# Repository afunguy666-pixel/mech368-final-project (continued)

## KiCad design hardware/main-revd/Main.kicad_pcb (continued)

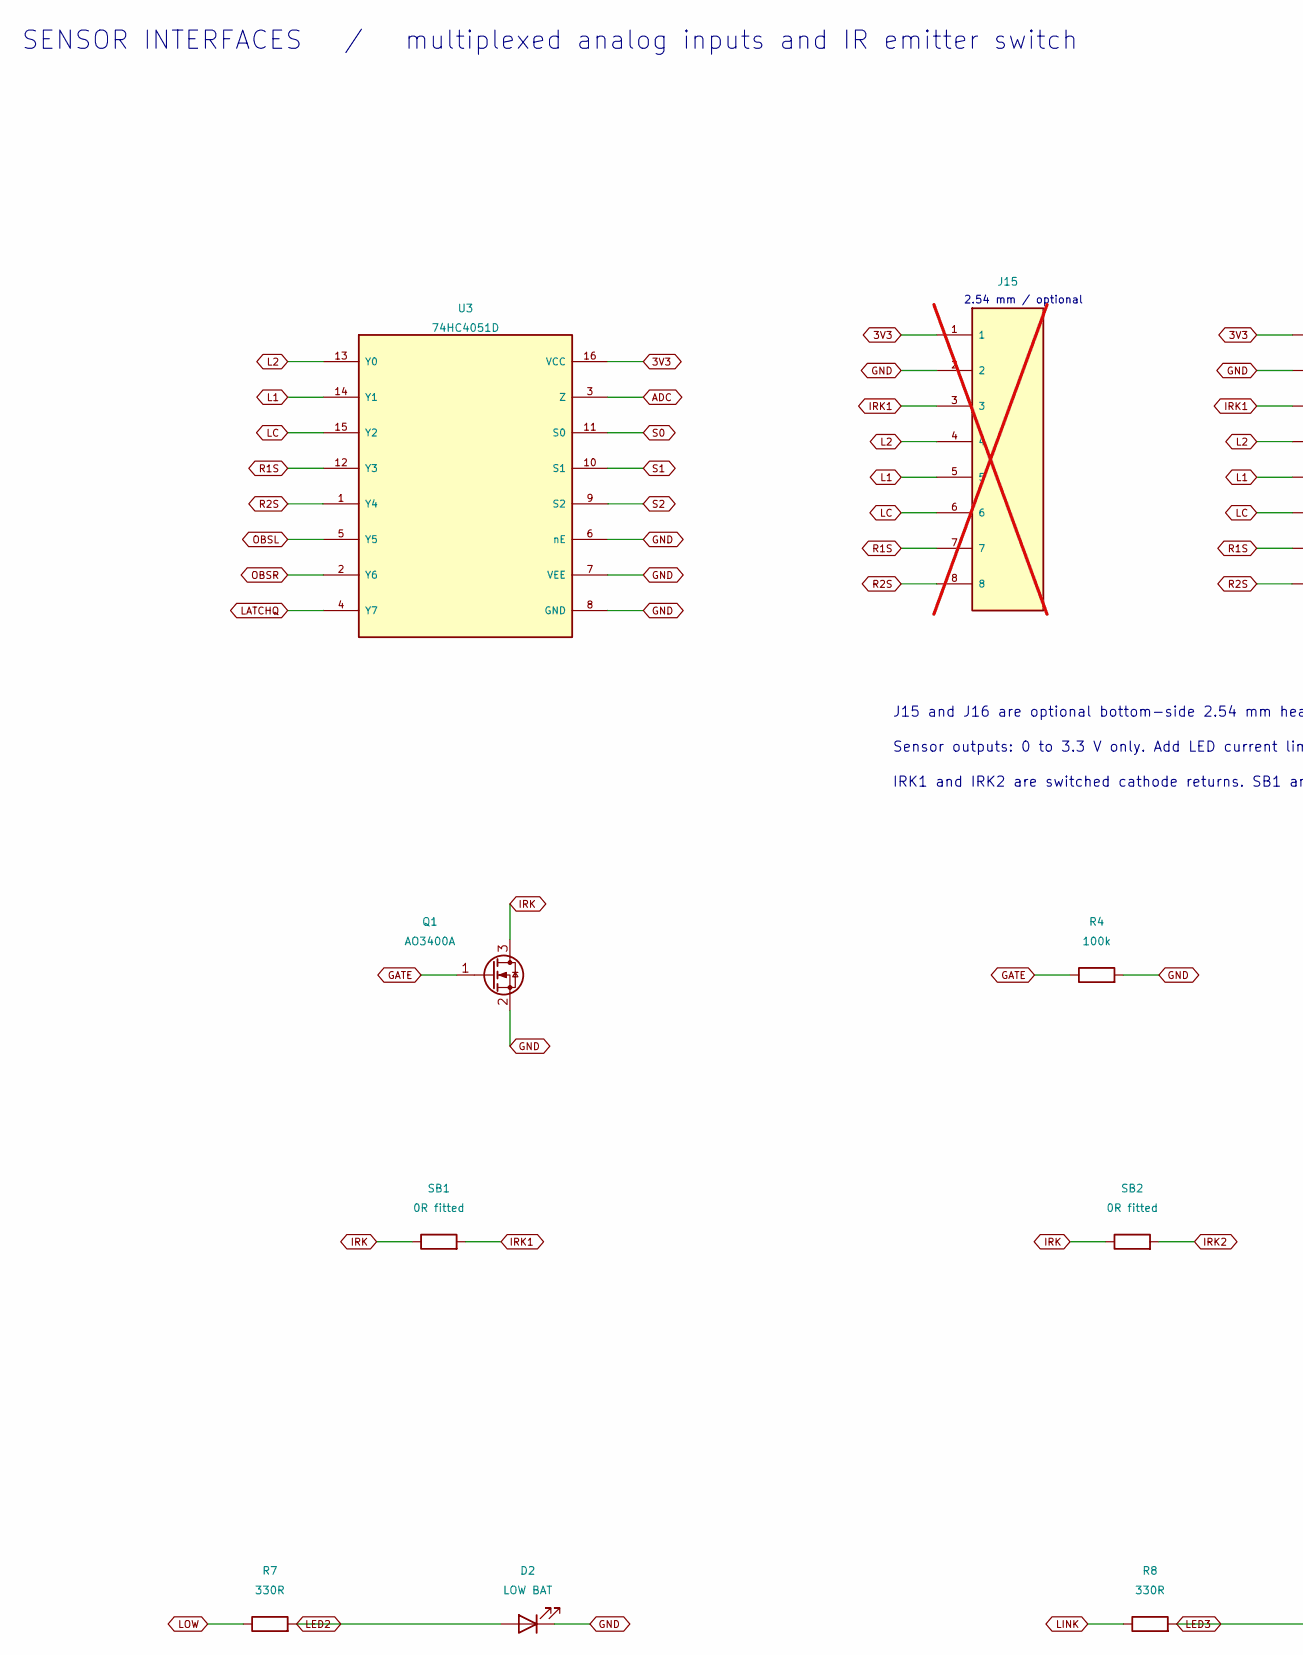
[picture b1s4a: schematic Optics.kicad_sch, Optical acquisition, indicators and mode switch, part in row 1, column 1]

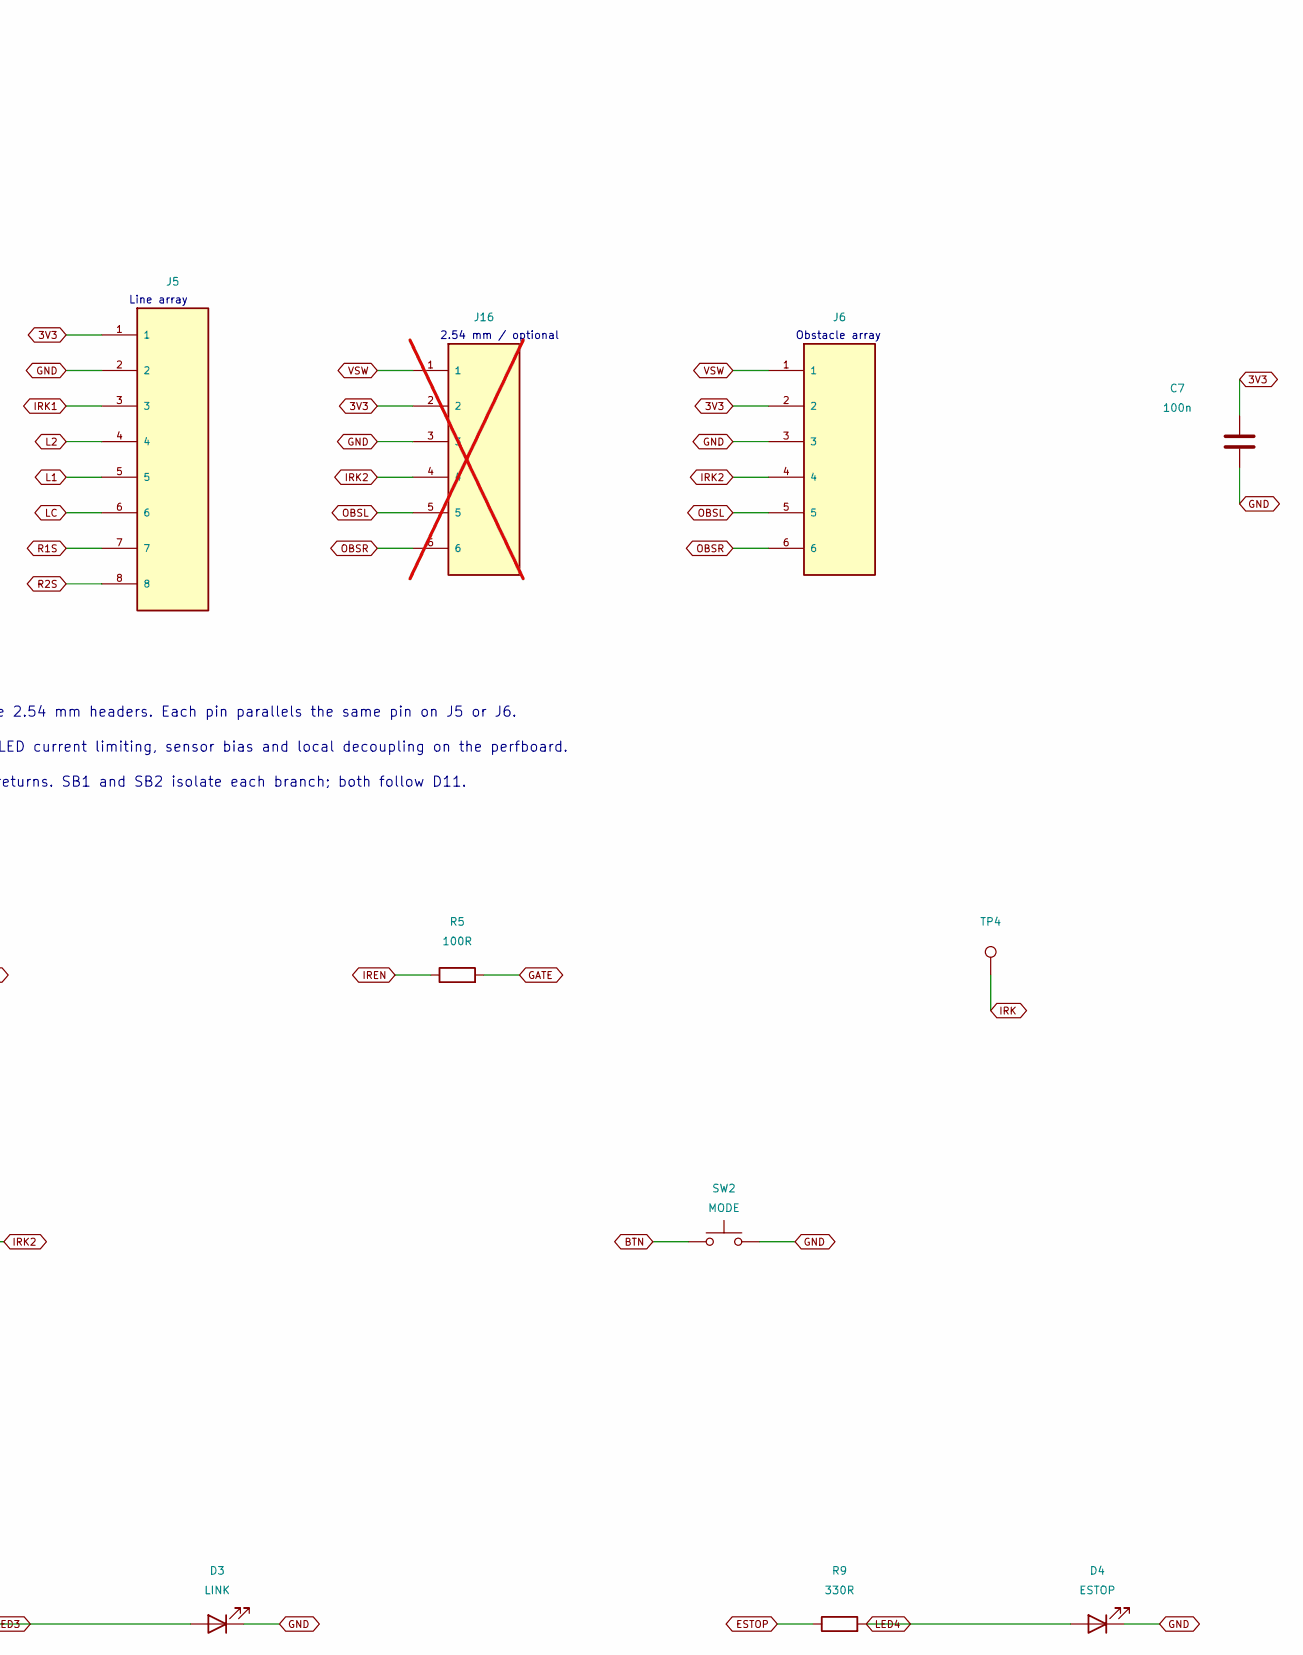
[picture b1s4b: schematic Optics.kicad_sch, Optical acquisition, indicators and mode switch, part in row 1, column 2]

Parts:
C7: 100n; C_0805_2012Metric
D2: LOW BAT; LED_D3.0mm
D3: LINK; LED_D3.0mm
D4: ESTOP; LED_D3.0mm
J5: XH; JST_XH_B8B-XH-A_1x08_P2.50mm_Vertical
J6: XH; JST_XH_B6B-XH-A_1x06_P2.50mm_Vertical
J15: Perfboard 2.54; PinHeader_1x08_P2.54mm_Vertical; not fitted
J16: Perfboard 2.54; PinHeader_1x06_P2.54mm_Vertical; not fitted
Q1: AO3400A; SOT-23
R4: 100k; R_Axial_DIN0207_L6.3mm_D2.5mm_P10.16mm_Horizontal
R5: 100R; R_Axial_DIN0207_L6.3mm_D2.5mm_P10.16mm_Horizontal
R7, R8, R9: 330R; R_Axial_DIN0207_L6.3mm_D2.5mm_P10.16mm_Horizontal
SB1, SB2: 0R fitted; R_Axial_DIN0207_L6.3mm_D2.5mm_P10.16mm_Horizontal
SW2: MODE; SW_PUSH_6mm
TP4: IRK; TestPoint_Pad_D1.5mm
U3: 74HC4051D; SOIC-16_3.9x9.9mm_P1.27mm

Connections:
3V3: C7.1, J5.1, J6.2, J15.1, J16.2, U3.16 (VCC); also elsewhere on the board
ADC: U3.3 (Z); also elsewhere on the board
BTN: SW2.1; also elsewhere on the board
ESTOP: R9.1; also elsewhere on the board
GATE: Q1.1 (G), R4.1, R5.2
GND: C7.2, D2.1 (K), D3.1 (K), D4.1 (K), J5.2, J6.3, J15.2, J16.3, Q1.2 (S), R4.2, SW2.2, U3.6 (nE), U3.7 (VEE), U3.8 (GND); also elsewhere on the board
IREN: R5.1; also elsewhere on the board
IRK: Q1.3 (D), SB1.1, SB2.1, TP4.1
IRK1: J5.3, J15.3, SB1.2
IRK2: J6.4, J16.4, SB2.2
L1: J5.5, J15.5, U3.14 (Y1)
L2: J5.4, J15.4, U3.13 (Y0)
LATCHQ: U3.4 (Y7); also elsewhere on the board
LC: J5.6, J15.6, U3.15 (Y2)
LED2: D2.2 (A), R7.2
LED3: D3.2 (A), R8.2
LED4: D4.2 (A), R9.2
LINK: R8.1; also elsewhere on the board
LOW: R7.1; also elsewhere on the board
OBSL: J6.5, J16.5, U3.5 (Y5)
OBSR: J6.6, J16.6, U3.2 (Y6)
R1S: J5.7, J15.7, U3.12 (Y3)
R2S: J5.8, J15.8, U3.1 (Y4)
S0: U3.11 (S0); also elsewhere on the board
S1: U3.10 (S1); also elsewhere on the board
S2: U3.9 (S2); also elsewhere on the board
VSW: J6.1, J16.1; also elsewhere on the board

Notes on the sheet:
SENSOR INTERFACES / multiplexed analog inputs and IR emitter switch
Line array
Obstacle array
2.54 mm / optional
J15 and J16 are optional bottom-side 2.54 mm headers. Each pin parallels the same pin on J5 or J6.
Sensor outputs: 0 to 3.3 V only. Add LED current limiting, sensor bias and local decoupling on the perfboard.
IRK1 and IRK2 are switched cathode returns. SB1 and SB2 isolate each branch; both follow D11.

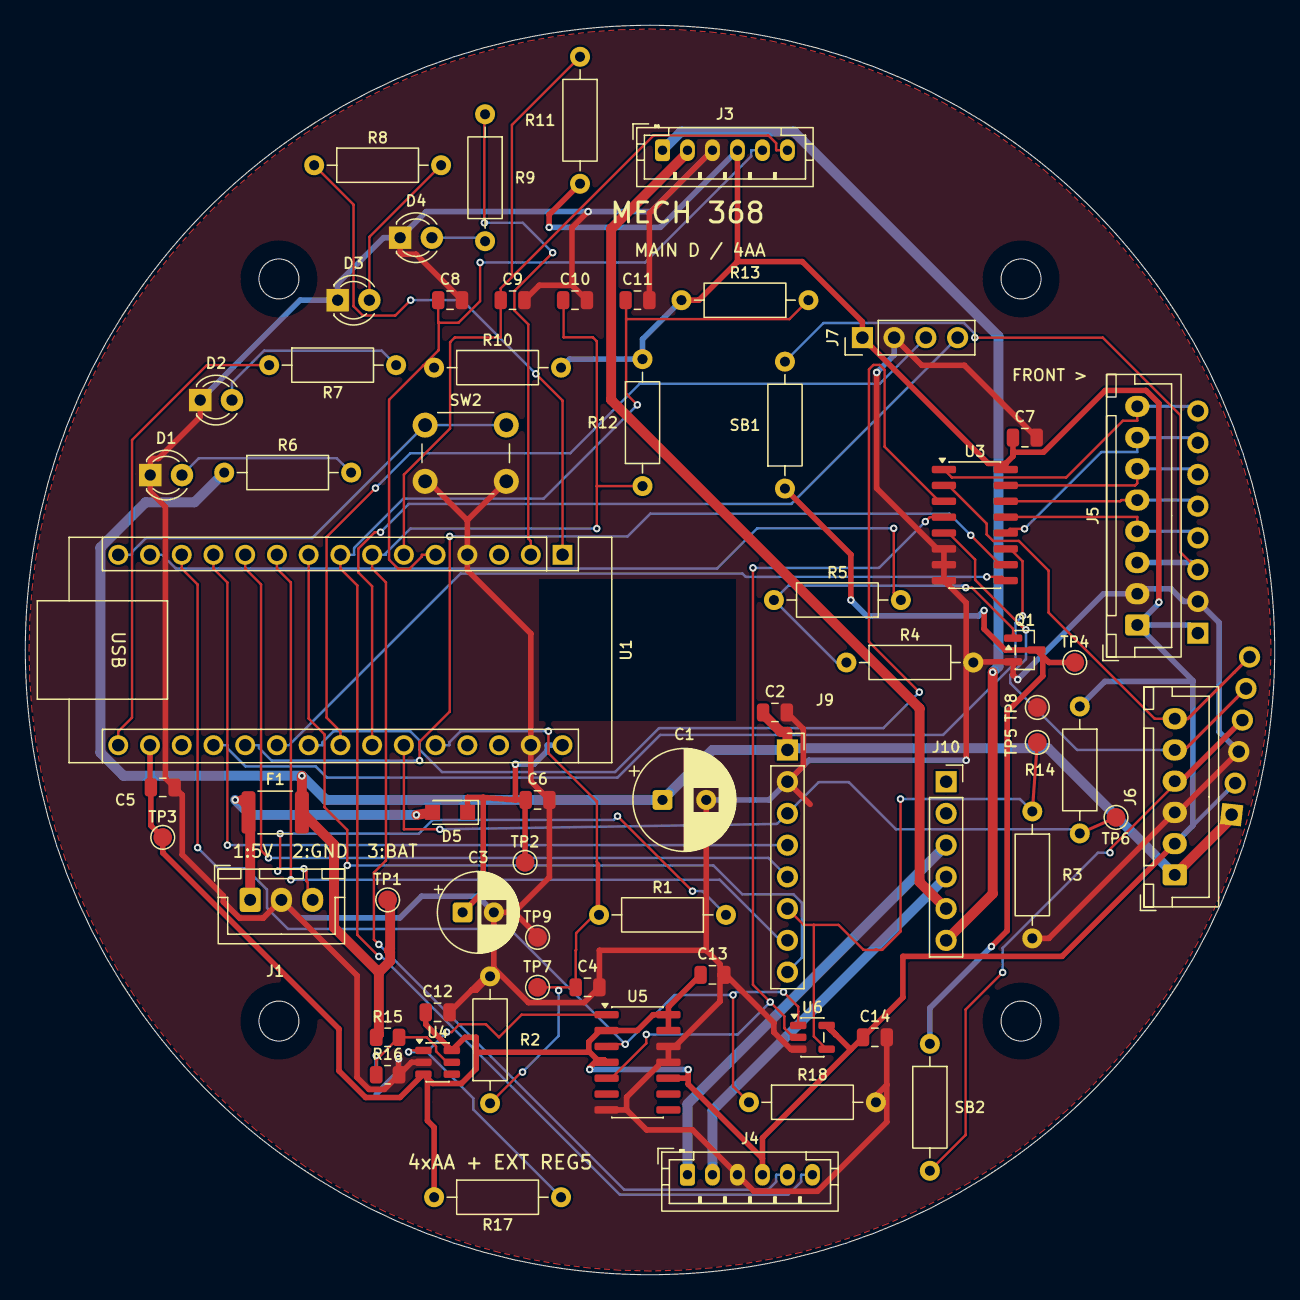
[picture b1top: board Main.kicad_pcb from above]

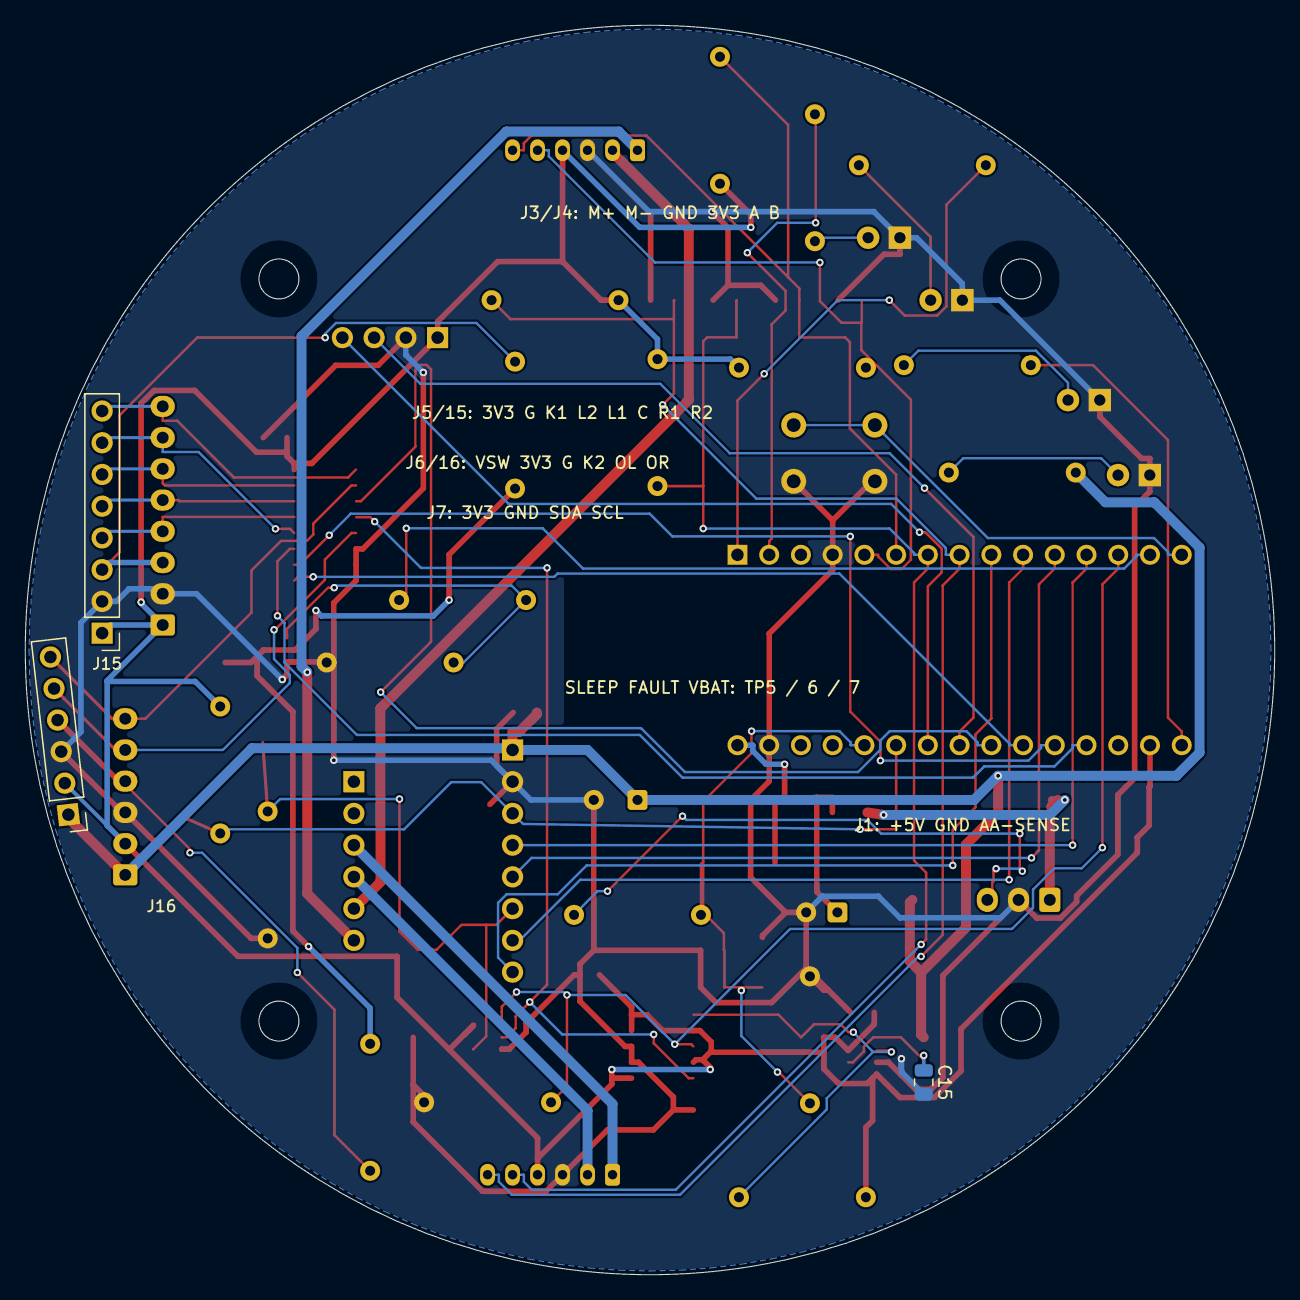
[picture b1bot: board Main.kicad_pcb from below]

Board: 2 copper layers, 100.0 x 100.0 mm, 71 parts (3 on the bottom side), 51 nets.

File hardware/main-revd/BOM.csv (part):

Reference,Value / part,Footprint,Population,Side,Sites,Pad nets,Assembly notes,Default sites for 5 boards,Supply group
C1,470u 16V,Capacitor_THT:CP_Radial_D8.0mm_P3.50mm,FIT,top,1,1=VSW | 2=GND,"Radial 470 uF, >=16 V, diameter <=8 mm, pitch 3.5 mm",5,Procure or existing bench stock
C2,100n,Capacitor_SMD:C_0805_2012Metric,FIT,top,1,1=VSW | 2=GND,,5,Procure or existing bench stock
C3,DNP 220u,Capacitor_THT:CP_Radial_D6.3mm_P2.50mm,DNP,top,1,1=VIN | 2=GND,,0,Optional / DNP
C4,100n,Capacitor_SMD:C_0805_2012Metric,FIT,top,1,1=VBAT_ADC | 2=GND,,5,Procure or existing bench stock
C5,100n,Capacitor_SMD:C_0805_2012Metric,FIT,top,1,1=3V3 | 2=GND,,5,Procure or existing bench stock
C6,10u 25V,Capacitor_SMD:C_0805_2012Metric,FIT,top,1,1=VIN | 2=GND,,5,Procure or existing bench stock
C7,100n,Capacitor_SMD:C_0805_2012Metric,FIT,top,1,1=3V3 | 2=GND,,5,Procure or existing bench stock
C8,DNP 100p,Capacitor_SMD:C_0805_2012Metric,DNP,top,1,1=ELA | 2=GND,,0,Optional / DNP
C9,DNP 100p,Capacitor_SMD:C_0805_2012Metric,DNP,top,1,1=ELB | 2=GND,,0,Optional / DNP
C10,DNP 100p,Capacitor_SMD:C_0805_2012Metric,DNP,top,1,1=ERA | 2=GND,,0,Optional / DNP
C11,DNP 100p,Capacitor_SMD:C_0805_2012Metric,DNP,top,1,1=ERB | 2=GND,,0,Optional / DNP
C12,100n,Capacitor_SMD:C_0805_2012Metric,FIT,top,1,1=3V3 | 2=GND,,5,Procure or existing bench stock
C13,100n,Capacitor_SMD:C_0805_2012Metric,FIT,top,1,1=3V3 | 2=GND,,5,Procure or existing bench stock
C14,100n,Capacitor_SMD:C_0805_2012Metric,FIT,top,1,1=3V3 | 2=GND,,5,Procure or existing bench stock
C15,DNP 10n,Capacitor_SMD:C_0805_2012Metric,DNP,bottom,1,1=UVS | 2=GND,"Optional UVS filter, X7R >=10 V; fit only if motor start/PWM transients falsely clear the latch (tau ~100 us)",0,Optional / DNP
D1,POWER,LED_THT:LED_D3.0mm,FIT,top,1,1=GND | 2=LED1,,5,Procure or existing bench stock
D2,LOW BAT,LED_THT:LED_D3.0mm,FIT,top,1,1=GND | 2=LED2,Visible low-battery indication,5,Procure or existing bench stock
D3,LINK,LED_THT:LED_D3.0mm,FIT,top,1,1=GND | 2=LED3,Visible BLE link / timeout indicator,5,Procure or existing bench stock
D4,ESTOP,LED_THT:LED_D3.0mm,FIT,top,1,1=GND | 2=LED4,Visible emergency stop indicator,5,Procure or existing bench stock
D5,PMEG2010ER K1,Diode_SMD:Nexperia_CFP3_SOD-123W,FIT,top,1,1=VIN | 2=REG5V,Nexperia PMEG2010ER; bar = pad 1 = VIN (east); anode on REG5V ahead of F1,5,Procure or existing bench stock
F1,1812L150/16DR 1.5A,Fuse:Fuse_1812_4532Metric,FIT,top,1,1=REG5V | 2=VSW,Littelfuse 1812L150/16DR; downstream PPTC,5,Procure or existing bench stock
H1,MountingHole_3.2mm_M3,MountingHole:MountingHole_3.2mm_M3,PCB FEATURE,top,1,,,0,PCB feature
H2,MountingHole_3.2mm_M3,MountingHole:MountingHole_3.2mm_M3,PCB FEATURE,top,1,,,0,PCB feature
H3,MountingHole_3.2mm_M3,MountingHole:MountingHole_3.2mm_M3,PCB FEATURE,top,1,,,0,PCB feature
H4,MountingHole_3.2mm_M3,MountingHole:MountingHole_3.2mm_M3,PCB FEATURE,top,1,,,0,PCB feature
J1,XH,Connector_JST:JST_XH_B3B-XH-A_1x03_P2.50mm_Vertical,FIT,top,1,1=REG5V | 2=GND | 3=RAW_AA,,5,Procure or existing bench stock
J3,PH,Connector_JST:JST_PH_B6B-PH-K_1x06_P2.00mm_Vertical,FIT,top,1,1=LPLUS | 2=LMINUS | 3=GND | 4=3V3 | 5=ELA | 6=ELB,,5,Procure or existing bench stock
J4,PH,Connector_JST:JST_PH_B6B-PH-K_1x06_P2.00mm_Vertical,FIT,top,1,1=RPLUS | 2=RMINUS | 3=GND | 4=3V3 | 5=ERA | 6=ERB,,5,Procure or existing bench stock
J5,XH,Connector_JST:JST_XH_B8B-XH-A_1x08_P2.50mm_Vertical,FIT,top,1,1=3V3 | 2=GND | 3=IRK1 | 4=L2 | 5=L1 | 6=LC | 7=R1S | 8=R2S,JST XH; pad 1 marked on board. 8 poles / XHP-8,5,Procure or existing bench stock
J6,XH,Connector_JST:JST_XH_B6B-XH-A_1x06_P2.50mm_Vertical,FIT,top,1,1=VSW | 2=3V3 | 3=GND | 4=IRK2 | 5=OBSL | 6=OBSR,JST XH; pad 1 marked on board. 6 poles / XHP-6,5,Procure or existing bench stock
J7,I2C,Connector_PinHeader_2.54mm:PinHeader_1x04_P2.54mm_Vertical,FIT,top,1,1=3V3 | 2=GND | 3=SDA | 4=SCL,,5,Procure or existing bench stock
J9,3297 JP5,Connector_PinSocket_2.54mm:PinSocket_1x08_P2.54mm_Vertical,FIT,top,1,1=VSW | 2=GND | 3=FAULT | 4=RP | 5=RD | 6=SLEEP | 7=LD | 8=LP,"Adafruit #3297 long socket, 1x8",5,Procure or existing bench stock
J10,3297 outputs/sense,Connector_PinSocket_2.54mm:PinSocket_1x06_P2.54mm_Vertical,FIT,top,1,1=unconnected-(J10-BSEN-Pad1) | 2=unconnected-(J10-ASEN-Pad2) | 3=RPLUS | 4=RMINUS | 5=LMINUS | 6=LPLUS,"Adafruit #3297 short socket, 1x6",5,Procure or existing bench stock
Q1,AO3400A,Package_TO_SOT_SMD:SOT-23,FIT,top,1,1=GATE | 2=GND | 3=IRK,,5,Procure or existing bench stock
R1,22k 1%,Resistor_THT:R_Axial_DIN0207_L6.3mm_D2.5mm_P10.16mm_Horizontal,FIT,top,1,1=RAW_AA | 2=VBAT_ADC,"BOJACK axial, top, 10.16 mm pitch, 0.8 mm finished drill. 22 kOhm upper divider, 1%",5,BOJACK kit
R2,10k 1%,Resistor_THT:R_Axial_DIN0207_L6.3mm_D2.5mm_P10.16mm_Horizontal,FIT,top,1,1=VBAT_ADC | 2=GND,"BOJACK axial, top, 10.16 mm pitch, 0.8 mm finished drill. 10 kOhm lower divider, 1%",5,BOJACK kit
R3,10k,Resistor_THT:R_Axial_DIN0207_L6.3mm_D2.5mm_P10.16mm_Horizontal,FIT,top,1,1=SLEEP | 2=GND,"BOJACK axial, top, 10.16 mm pitch, 0.8 mm finished drill. ",5,BOJACK kit
R4,100k,Resistor_THT:R_Axial_DIN0207_L6.3mm_D2.5mm_P10.16mm_Horizontal,FIT,top,1,1=GATE | 2=GND,"BOJACK axial, top, 10.16 mm pitch, 0.8 mm finished drill. ",5,BOJACK kit
R5,100R,Resistor_THT:R_Axial_DIN0207_L6.3mm_D2.5mm_P10.16mm_Horizontal,FIT,top,1,1=IREN | 2=GATE,"BOJACK axial, top, 10.16 mm pitch, 0.8 mm finished drill. ",5,BOJACK kit
R6,2.2k,Resistor_THT:R_Axial_DIN0207_L6.3mm_D2.5mm_P10.16mm_Horizontal,FIT,top,1,1=VSW | 2=LED1,"BOJACK axial, top, 10.16 mm pitch, 0.8 mm finished drill. ",5,BOJACK kit
R7,330R,Resistor_THT:R_Axial_DIN0207_L6.3mm_D2.5mm_P10.16mm_Horizontal,FIT,top,1,1=LOW | 2=LED2,"BOJACK axial, top, 10.16 mm pitch, 0.8 mm finished drill. ",5,BOJACK kit
R8,330R,Resistor_THT:R_Axial_DIN0207_L6.3mm_D2.5mm_P10.16mm_Horizontal,FIT,top,1,1=LINK | 2=LED3,"BOJACK axial, top, 10.16 mm pitch, 0.8 mm finished drill. ",5,BOJACK kit
R9,330R,Resistor_THT:R_Axial_DIN0207_L6.3mm_D2.5mm_P10.16mm_Horizontal,FIT,top,1,1=ESTOP | 2=LED4,"BOJACK axial, top, 10.16 mm pitch, 0.8 mm finished drill. ",5,BOJACK kit
R10,DNP 10k,Resistor_THT:R_Axial_DIN0207_L6.3mm_D2.5mm_P10.16mm_Horizontal,DNP,top,1,1=ELA | 2=3V3,"Optional encoder pull-up; BOJACK axial, top, 10.16 mm pitch, 0.8 mm finished drill. ",0,Optional BOJACK kit
R11,DNP 10k,Resistor_THT:R_Axial_DIN0207_L6.3mm_D2.5mm_P10.16mm_Horizontal,DNP,top,1,1=ELB | 2=3V3,"Optional encoder pull-up; BOJACK axial, top, 10.16 mm pitch, 0.8 mm finished drill. ",0,Optional BOJACK kit
R12,DNP 10k,Resistor_THT:R_Axial_DIN0207_L6.3mm_D2.5mm_P10.16mm_Horizontal,DNP,top,1,1=ERA | 2=3V3,"Optional encoder pull-up; BOJACK axial, top, 10.16 mm pitch, 0.8 mm finished drill. ",0,Optional BOJACK kit
R13,DNP 10k,Resistor_THT:R_Axial_DIN0207_L6.3mm_D2.5mm_P10.16mm_Horizontal,DNP,top,1,1=ERB | 2=3V3,"Optional encoder pull-up; BOJACK axial, top, 10.16 mm pitch, 0.8 mm finished drill. ",0,Optional BOJACK kit
R14,10k,Resistor_THT:R_Axial_DIN0207_L6.3mm_D2.5mm_P10.16mm_Horizontal,FIT,top,1,1=3V3 | 2=FAULT,"BOJACK axial, top, 10.16 mm pitch, 0.8 mm finished drill. ",5,BOJACK kit
R15,110k 0.1%,Resistor_SMD:R_0805_2012Metric,FIT,top,1,1=VSW | 2=UVS,"110 kOhm upper supervisor divider, 0.1%",5,Procure or existing bench stock
R16,11.0k 0.1%,Resistor_SMD:R_0805_2012Metric,FIT,top,1,1=UVS | 2=GND,"11.0 kOhm lower supervisor divider, 0.1%; trip ~4.455 V",5,Procure or existing bench stock
R17,10k,Resistor_THT:R_Axial_DIN0207_L6.3mm_D2.5mm_P10.16mm_Horizontal,FIT,top,1,1=3V3 | 2=CLR,"BOJACK axial, top, 10.16 mm pitch, 0.8 mm finished drill. ",5,BOJACK kit
R18,10k,Resistor_THT:R_Axial_DIN0207_L6.3mm_D2.5mm_P10.16mm_Horizontal,FIT,top,1,1=ARM | 2=GND,"BOJACK axial, top, 10.16 mm pitch, 0.8 mm finished drill. ",5,BOJACK kit
SB1,0R fitted,Resistor_THT:R_Axial_DIN0207_L6.3mm_D2.5mm_P10.16mm_Horizontal,FIT,top,1,1=IRK | 2=IRK1,"BOJACK axial, top, 10.16 mm pitch, 0.8 mm finished drill. ",5,BOJACK kit
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
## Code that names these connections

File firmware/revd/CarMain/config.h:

#pragma once
// MECH 368 双轮巡线车 · 主控固件配置
// 引脚和可调参数集中在这里。换板只改 BOARD；标 TODO 的数值要按实车测量后填。

#include <Arduino.h>

// ───────────────────────── 1. 选择硬件 ─────────────────────────
#define BOARD_REVD       1   // RevD PCB（5 路巡线、多路器、锁存器）
#define BOARD_PERFBOARD  2   // 洞洞板版（3 路巡线直连 A0–A2，SLP 直接由 D10 控制）
#ifndef BOARD
#define BOARD BOARD_REVD
#endif

#ifndef USE_BLE
#define USE_BLE 1            // 0 = 不编译蓝牙，只用 USB 串口台架调试
#endif
#ifndef USE_GESTURE
#define USE_GESTURE 1        // 板载 APDS9960 手势：本地解除急停 / 启动自主
#endif

// ───────────────────────── 2. 引脚 ─────────────────────────
#if BOARD == BOARD_REVD
  // 电机（DRV8833 #3297）：每轮 IN1 输出 PWM，IN2 作方向
  #define PIN_L_IN1     6    // LP
  #define PIN_L_IN2     7    // LD
  #define PIN_R_IN1     9    // RP
  #define PIN_R_IN2     8    // RD
  #define PIN_ARM       10   // 电机许可：上升沿置位锁存；低电平立即停机
  #define PIN_IREN      11   // Q1：IR 发射管总开关，高 = 亮
  #define PIN_BTN       12   // SW2 MODE，按下接地
  #define PIN_LED_LOW   13   // D2 LOW BAT
  #define PIN_LED_LINK  1    // D3 LINK（Nano TX 脚）
  #define PIN_LED_ESTOP 0    // D4 ESTOP（Nano RX 脚）
  #define PIN_ENC_LA    2
  #define PIN_ENC_LB    3
  #define PIN_ENC_RA    4
  #define PIN_ENC_RB    5
  #define PIN_MUX_S0    A0
  #define PIN_MUX_S1    A1
  #define PIN_MUX_S2    A2
  #define PIN_MUX_Z     A3
  #define PIN_FAULT     A6   // DRV8833 nFAULT，低 = 过流/过热
  #define PIN_VBAT      A7   // RAW_AA 经 22k/10k 分压

  #define HAS_MUX       1
  #define HAS_LATCH     1
  #define HAS_IR_SWITCH 1
  #define HAS_LEDS      1
  #define HAS_BUTTON    1
  #define HAS_VBAT      1
  #define HAS_FAULT     1

  #define NUM_LINE 5
  // HAS_MUX = 1 时填 74HC4051 通道号。巡线从左到右排列。
  static const uint8_t LINE_SRC[NUM_LINE] = {0, 1, 2, 3, 4};  // L2 L1 LC R1S R2S
  static const uint8_t OBS_SRC[2]         = {5, 6};           // OBSL OBSR
  #define MUX_CH_LATCH 7                                       // LATCHQ

#elif BOARD == BOARD_PERFBOARD
  #define PIN_L_IN1     6    // AIN1
  #define PIN_L_IN2     7    // AIN2
  #define PIN_R_IN1     9    // BIN1
  #define PIN_R_IN2     8    // BIN2
  #define PIN_ARM       10   // 直接接 SLP
  #define PIN_ENC_LA    2    // 洞洞板需另焊编码器线
  #define PIN_ENC_LB    3
  #define PIN_ENC_RA    4
  #define PIN_ENC_RB    5

  #define HAS_MUX       0
  #define HAS_LATCH     0
  #define HAS_IR_SWITCH 0
  #define HAS_LEDS      0
  #define HAS_BUTTON    0
  #define HAS_VBAT      0
  #define HAS_FAULT     0

  #define NUM_LINE 3
  // HAS_MUX = 0 时直接填模拟引脚
  static const uint8_t LINE_SRC[NUM_LINE] = {A0, A1, A2};     // 左 中 右
  static const uint8_t OBS_SRC[2]         = {A3, A6};         // 左 右避障（需另焊）
#else
  #error "未知 BOARD"
#endif

// ───────────────────────── 3. 传感器 ─────────────────────────
#define ADC_BITS            12
#define ADC_MAX             4095
#define MUX_SETTLE_US       20
#define IR_SETTLE_US        300    // TODO 发射管开关后光电管的稳定时间，示波器实测后可调小
#define SENSOR_ACTIVE_LOW   1      // 光电管上拉接法：反光越强，输出电压越低
#define LINE_IS_DARK        1      // 1 = 白底黑线；0 = 黑底白线
#define LINE_NOISE_FLOOR    0.15f  // 归一化后低于此值的“线强度”视为背景
#define LINE_FOUND_THRESH   0.45f  // 最暗的一路超过此值才认为看到线
#define CALIBRATE_MS        3000   // 校准时长：期间手推车体让每个探头扫过黑线和白底

#define OBS_MODE_ANALOG_DIFF 0     // 自制 IR 对管，发射管经 Q1 开关，取亮暗差值
#define OBS_MODE_DIGITAL_LOW 1     // FC-51 一类成品模块：有障碍输出低。模块必须用 3V3 供电
#ifndef OBS_MODE
#define OBS_MODE OBS_MODE_DIGITAL_LOW
#endif
#define OBS_THRESHOLD       600    // ANALOG_DIFF 模式的差值门限（12 位 ADC 计数）
#define OBS_DEBOUNCE        3      // 连续 N 帧结果一致才改变障碍状态

// ───────────────────────── 4. 电池 ─────────────────────────
#define VBAT_DIVIDER        3.2f   // (22k + 10k) / 10k
#define VBAT_ADC_REF        3.3f
#define VBAT_LOW_V          4.4f   // 4 × 1.10 V：LOW BAT 灯亮
#define VBAT_CRIT_V         4.0f   // 4 × 1.00 V：持续 VBAT_CRIT_MS 后停机
#define VBAT_CRIT_MS        500

// ───────────────────────── 5. 电机与编码器 ─────────────────────────
#define PWM_FREQ_HZ         20000  // 20 kHz，听不到电机啸叫
#define MOTOR_L_INVERT      0      // TODO 串口 't' 测试后，哪个轮子反转就把对应项改 1
#define MOTOR_R_INVERT      0
#define MOTOR_DEADBAND      0.02f

#define ENC_X4              0      // 0 = 只用 A 相边沿（×2，中断少一半）；1 = A/B 都用（×4）
#define ENC_L_INVERT        0      // TODO 轮子正转时计数应增加，否则改 1
#define ENC_R_INVERT        0
#define ENC_COUNTS_PER_REV  1400   // TODO 轮子转一圈的计数（电机 PPR × 减速比 × 2 或 4）
#define WHEEL_DIAMETER_MM   65.0f  // TODO
#define MAX_WHEEL_CPS       3000.0f // TODO 满 PWM、架空时的计数/秒，串口 't' 测试可读出

#define USE_SPEED_LOOP      0      // 编码器方向确认无误后改 1，启用轮速闭环
#define SPEED_KP            0.6f
#define SPEED_KI            4.0f

// ───────────────────────── 6. 运动控制 ─────────────────────────
#define CONTROL_HZ          100
#define AUTO_BASE_SPEED     0.45f  // 自主模式直道速度（-1..1）
#define LINE_KP             0.6f
#define LINE_KI             0.0f
#define LINE_KD             0.05f
#define LOST_SEARCH_SPEED   0.30f  // 丢线后朝最后一次看到线的方向原地转
#define LOST_TIMEOUT_MS     1500   // 超时仍找不到线就停机
#define MANUAL_MAX          0.8f   // 遥控模式最大输出

// ───────────────────────── 7. 通信与安全 ─────────────────────────
#define BLE_NAME            "MECH368-CAR-01"  // 每台车改成不同名字，遥控器按名字连接
#define LINK_TIMEOUT_MS     500    // 超过此时间没收到遥控器任何命令 → 急停
#define REQUIRE_LINK_IN_AUTO 1     // 1 = 自主模式也要求遥控器在线，遥控急停始终有效
#define TELEMETRY_MS        100
#define DEBUG_PRINT_MS      200
#define BTN_LONG_MS         1500
#define GESTURE_POLL_MS     50
